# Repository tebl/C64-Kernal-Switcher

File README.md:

# C64 Kernal Switcher

Originally started this design with the idea of using an Arduino as a way to switch between Commodore 64 kernal ROMs, but ended up adapting BWACKs design into it instead and like him opted for the PIC12F629 instead. This particular version of a quad kernal switcher for the Commodore 64 is only compatible with Commodore 64 "longboards" (usually breadbins, but you never really know what you get with Commodore so check first).

BWACKs design has been adapted into mine, changing along the way a few of the features to my liking - in particular, reusing the original power LEDs as well as support for manual switches (find it more adaptable that way). Original pinouts and RGB headers have been kept the same in order to not have to do a manual like he did, but note that I've rotated them for easier use with angled pin headers to save on space within the newer and tighter C64C-style cases. Reusing the original LED makes it easier because RGB LEDs in a size that fits a C64C case is harder to find, not to mention fiddly to wire up for beginners with access to a soldering iron.

With only the single LED available, the code supplied with this project has been rewritten so that when you hold down the RESTORE it counts the flashes - then when you let go it performs the actions according to the following list:

1. RESET
2. Next kernal
3. Kernal 0
4. Kernal 1
5. Kernal 2
6. Kernal 3

The board itself should be functionally identical to the one made by [bwack](https://github.com/bwack/C64-Switchless-Multi-Kernal-27C256-adapter), if you want the original behavior using the RGB header with an RGB LED - use the code provided with that project.

## Building the switcher
Soldering together the few components should be easy going as long as you have access to reasonable tools, personally I'm using a cheap soldering station with adjustable temperature so no need to go expensive if you don't have to. Use 60/40 soldering tin, the lead free makes to job a lot harder if you're new to the hobby.

Start by studying the PCB, both sides and perform dry fits to see that you have an idea of where everything goes since removing things is always a lot harder than getting it right in the first place (match orientation to symbols, see gallery images for reference).

With a lot going on for such a tiny board, you'd need to pay some attention to the sequence of components getting soldered in. The list below is the one I recommend, note that with some sockets you'll have less space underneath and it'll be a lot easier getting it into place if you trim the pins after they have been soldered into place. When aligning the two 12-pin (round) pin-headers I recommend using a round-pin socket to help keep them straight, that way you won't get issues trying to install it into the Commodore 64.

1. Resistors
2. 8-pin socket (solder on reverse-side)
3. 12pin-header on the right side (solder on reverse-side)
4. 28-pin socket
5. 12-pin header on the left side (solder on reverse-side)
6. Capacitor
7. Remaining pin headers as needed

### Alternative build
The PCB doubles up as a 27c256 to 2364 adapter board, which means that you can also use it to replace the other ROM ICs used in the longboard versions of the motherboard. While there aren't many alternatives available for the basic and character ROM, but replacing them may lead to lower power use as well as decreased heat within the computer case - personally I use one as a handy way of having a 4-in-1 replacement when troubleshooting failed systems. The build process is the same as the one above, but there is no need to add resistors, 12-pin socket since the 12f629 won't be used and then add pin headers at the top in order select active ROM image. You can generate a suitable bin-file to flash 27c256 using the following command (substitute kernal4 with one of your own choice):

`copy /b basic.901226-01.bin+kernal.901227-03.bin+characters.901225-01.bin+kernal4.bin 27C256_longboard_4in1.bin`

## Installation
First of all, check that you have a C64 with a "longboard", these are physically larger - the later common C64C boards had combined basic and kernal ROMs on a single chip, requiring a different solution altogether! First locate the kernal ROM, it should be marked 901227-03 and preferably already socketed.

If it is not socketed and you don't have experience desoldering ICs from older PCBs, I would suggest that you have someone with more experience perform this task for you - if you still go through with it, you live with the consequences! If you are really doing it anyway, cut off all the legs as close to the IC as possible and then remove leftovers with tweezers and solder-braid - IC will be dead, but the board itself will probably be happier!

When installing in the computer, the pin on the bottom are inserted into the socket. You'll now need to find suitable places to attach the signal wires to the mainboard, you'll need to find a spot for the RESET and the RESTORE lines. RESET will have continuity to pin 40 on the 6510 processor, a spot for RESTORE can be found by tracing from pin 3 of the keyboard connector (pin 2 is missing). As with all things Commodore, Ray Carlsen will probably have a picture of those points for your specific revision so take a look [http://personalpages.tds.net/~rcarlsen/cbm/switchless%20JiffyDOS/](http://personalpages.tds.net/~rcarlsen/cbm/switchless%20JiffyDOS/).

## Kernals
There have been made several kernals for the Commodore 64, this solution allows you to add 3 other kernals in addition to the original one (you'll need it for compatibility). Among my favourites are the [SD2IEC Kernal ROM](https://csdb.dk/release/?id=159050), [Turbo Tape Kernal ROM](https://csdb.dk/release/?id=47403) and [JiffyDOS](http://www.go4retro.com/products/jiffydos/). Note that JiffyDOS, while a popular choice is still under license so you should therefore seek to obtain a registered license for it!

On windows you can generate a 32kb file with your selected kernals by using the copy command, this can then be flashed to a blank 27C256 EPROM. Substitute kernals 2-4 with those of your choice:

`copy /b kernal.901227-03.bin+kernal2.bin+kernal3.bin+kernal4.bin 27C256_breadbin.bin`

# Original design
As a large part of this project, schematic and code, was based on the one originally made by bwack, I've included the following section from that projects README.txt here in accordance with the license specified.

> C64 Switchless Multi Kernel Switch
> \- 27C256 rom adapter for C64's with long motherboard

> Designed by BWACK.
> CERN OPEN HARDWARE LICENSE v1.2
> http://www.ohwr.org/

> The Eagle CAD files are available on GitHub:
> https://github.com/bwack/C64-Switchless-Multi-Kernal-27C256-adapter

> All text above must be included in any redistribution

# Schematic
The supplied KiCad files should be sufficient as both a schematic and as a  starting point for ordering PCBs (basically you could just zip the contents of the export folder and upload that on a fabrication site), the schematic is also available in [PDF-format](https://github.com/tebl/C64_Kernal_Switcher/raw/master/export/C64%20Kernal%20Switcher.pdf) and this is what you'll need to print and work your way through this things don't work as expected after assembly.

# BOM
Most parts should be easy to get a hold of from your favourite local electronic component shop, but given that I don't have access to such shops where I live so everything was based on whatever I could get cheapest from ebay/AliExpress (free shipping, plan on usually waiting 3-4 weeks though). The list below should be everything you'll need in addition to a workable soldering iron and some 60/40 soldering tin. Other tools needed for this project is an EPROM-ereaser as well as an EPROM-programmer for the two ICs (I use MiniPro TL866 for both).

Pin headers you order in bulk and snap off parts as needed, but note that you should get round pin headers for the part that goes into the socket - while you can use the regular kind, you may easily wear out or break the socket.

Components in parenthesis are those used for extra features, you can omit these if you want to or have no need of those features (adding switches makes no sense if using MCU). RGB header can be left off, this is optional if you wish to use code from the original project! Sockets are always recommended though technically not needed.

| Reference    | Item                                  | Count |
| ------------ | ------------------------------------- | ----- |
| PCB          | Fabricate using Gerber files ([order](https://www.pcbway.com/project/shareproject/Commodore_64_Quad_Kernal_Switcher.html?inviteid=88707))          |     1 |
| C1           | 100nF capacitor                       |     1 |
| R1           | 1k ohm resistor                       |   (1) | 
| R2           | 3k3 ohm resistor                      |   (1) |
| R3           | 560 ohm resistor                      |     1 |
| U1           | 12-pin straight round header          |     2 |
| U2           | PIC12F629 DIP-8                       |     1 |
| U2 (socket)  | 8-pin socket                          |   (1) |
| U3           | 27C256 EPROM DIP-28                   |     1 |
| U3 (socket)  | 28-pin wide socket                    |   (1) |
| A13,A14      | 3-pin straight header                 |   (2) |
| Signal, LED  | 3-pin angled header                   |     2 |
| RGB          | 2x3-pin straight header               |   (1) |

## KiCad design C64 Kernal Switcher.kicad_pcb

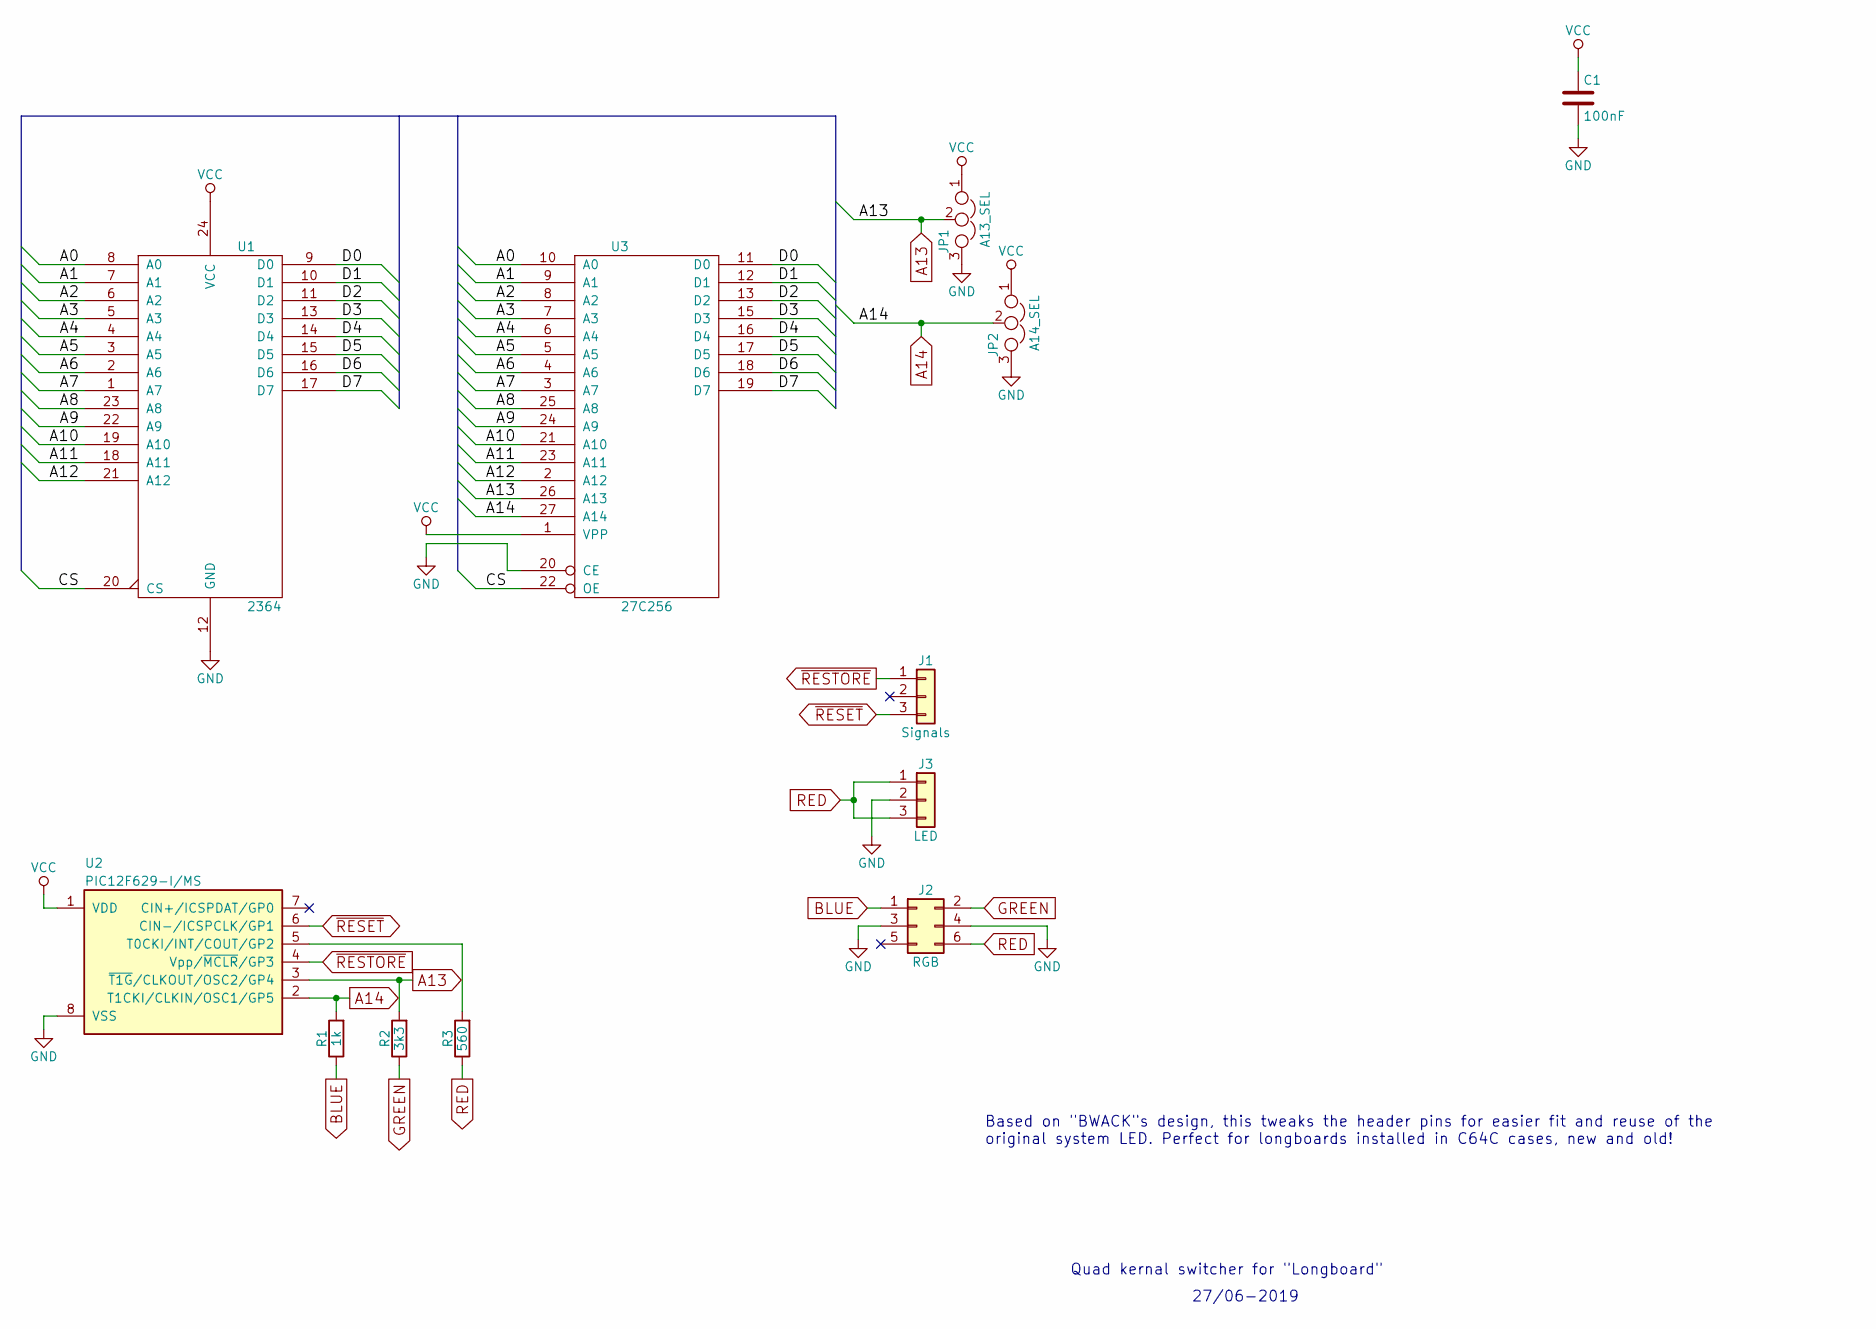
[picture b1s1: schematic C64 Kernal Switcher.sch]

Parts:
C1: 100nF; C_Disc_D4.7mm_W2.5mm_P5.00mm
J1: Signals; Pin_Header_Angled_1x03_Pitch2.54mm
J2: RGB; Pin_Header_Straight_2x03_Pitch2.54mm
J3: LED; Pin_Header_Angled_1x03_Pitch2.54mm
JP1: A13_SEL; Pin_Header_Straight_1x03_Pitch2.54mm
JP2: A14_SEL; Pin_Header_Straight_1x03_Pitch2.54mm
R1: 1k; R_Axial_DIN0207_L6.3mm_D2.5mm_P10.16mm_Horizontal
R2: 3k3; R_Axial_DIN0207_L6.3mm_D2.5mm_P10.16mm_Horizontal
R3: 560; R_Axial_DIN0207_L6.3mm_D2.5mm_P10.16mm_Horizontal
U1: 2364; DIP-24_W15.24mm_Socket
U2: PIC12F629-I/MS; DIP-8_W7.62mm_Socket
U3: 27C256; DIP-28_W15.24mm_Socket

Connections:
/A0: U1.8 (A0), U3.10 (A0)
/A1: U1.7 (A1), U3.9 (A1)
/A2: U1.6 (A2), U3.8 (A2)
/A3: U1.5 (A3), U3.7 (A3)
/A4: U1.4 (A4), U3.6 (A4)
/A5: U1.3 (A5), U3.5 (A5)
/A6: U1.2 (A6), U3.4 (A6)
/A7: U1.1 (A7), U3.3 (A7)
/A8: U1.23 (A8), U3.25 (A8)
/A9: U1.22 (A9), U3.24 (A9)
/A10: U1.19 (A10), U3.21 (A10)
/A11: U1.18 (A11), U3.23 (A11)
/A12: U1.21 (A12), U3.2 (A12)
/CS: U1.20 (CS), U3.22 (OE)
/D0: U1.9 (D0), U3.11 (D0)
/D1: U1.10 (D1), U3.12 (D1)
/D2: U1.11 (D2), U3.13 (D2)
/D3: U1.13 (D3), U3.15 (D3)
/D4: U1.14 (D4), U3.16 (D4)
/D5: U1.15 (D5), U3.17 (D5)
/D6: U1.16 (D6), U3.18 (D6)
/D7: U1.17 (D7), U3.19 (D7)
A13: JP1.2, R2.2, U2.3 (~T1G~/CLKOUT/OSC2/GP4), U3.26 (A13)
A14: JP2.2, R1.2, U2.2 (T1CKI/CLKIN/OSC1/GP5), U3.27 (A14)
BLUE: J2.1, R1.1
GND: C1.2, J2.3, J2.4, J3.2, JP1.3, JP2.3, U1.12 (GND), U2.8 (VSS), U3.14 (GND), U3.20 (CE)
GREEN: J2.2, R2.1
unnamed: R3.2, U2.5 (T0CKI/INT/COUT/GP2)
RED: J2.6, J3.1, J3.3, R3.1
VCC: C1.1, JP1.1, JP2.1, U1.24 (VCC), U2.1 (VDD), U3.1 (VPP), U3.28 (VCC)
~RESET: J1.3, U2.6 (CIN-/ICSPCLK/GP1)
~RESTORE: J1.1, U2.4 (Vpp/~MCLR~/GP3)

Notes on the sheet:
Quad kernal switcher for "Longboard"
Based on "BWACK"s design, this tweaks the header pins for easier fit and reuse of the original system LED. Perfect for longboards installed in C64C cases, new and old!
27/06-2019

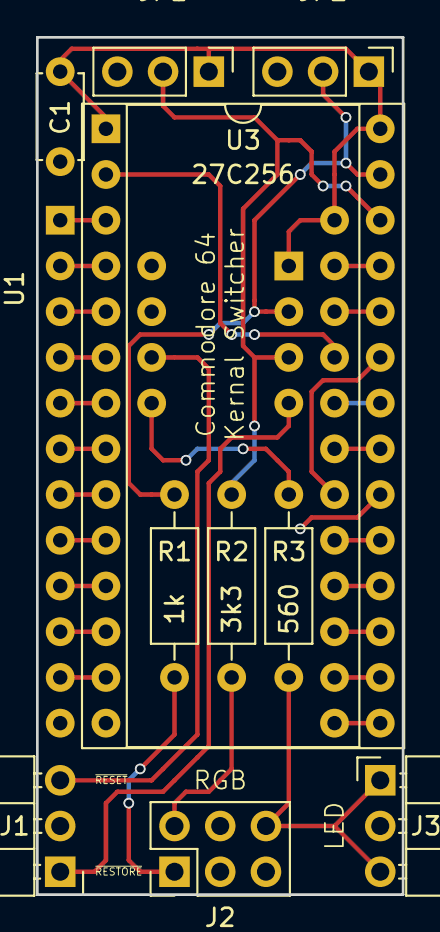
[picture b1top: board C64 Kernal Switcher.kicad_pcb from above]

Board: 2 copper layers, 20.3 x 47.6 mm, 12 parts (1 on the bottom side), 32 nets.

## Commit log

2019-04-29 Basic schematic
2019-04-29 Fixed footprints
2019-04-29 Deleted local copy
2019-04-29 PCB layed out, need measuring
2019-06-17 Changed to PIC like bwack's design
2019-06-17 Assigned footprints
2019-06-17 mysensors no longer used
2019-06-17 Layout redone
2019-06-17 Use original license
2019-06-17 Added updated code
2019-06-17 Updated silkscreen
2019-06-17 Updated gitignore
2019-06-17 Gerber export
2019-06-17 Added change notes to code
2019-06-23 Added untested notice
2019-06-27 Moved R1 so it fits better under socket
2019-06-27 Tweaked code so that blink is more visible, less waiting...
2019-06-27 Added gallery images
2019-06-27 Rotated images
2019-06-27 Fixed URL
2019-08-08 Alternative build details
